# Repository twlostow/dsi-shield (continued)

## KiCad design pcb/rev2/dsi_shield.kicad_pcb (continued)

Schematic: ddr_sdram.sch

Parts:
C11, C65, C67, C71, C72, C73, C75: CC0603_100NF_100V_10%_X7R; CAPC1608X90N; Voltage 100V; Tolerance ±10%; Part Number CC0603_100NF_100V_10%_X7R
C64: CC0603_1UF_50V_10%_X5R; CAPC1608X87N; Voltage 50V; Tolerance ±10%; Part Number CC0603_1UF_50V_10%_X5R
C66, C68, C69, C70: CC0603_10NF_50V_10%_X7R; CAPC1608X87N; Voltage 50V; Tolerance ±10%; Part Number CC0603_10NF_50V_10%_X7R
IC10: MT46V32M16P-5B:F; TSOP66
R67: R0603_100R_1%_0.1W_100PPM; RESC1608X55N; Voltage ~~; Tolerance ±1%; Part Number R0603_100R_1%_0.1W_100PPM
R68, R69: R0603_1K_1%_0.1W_100PPM; RESC1608X55N; Voltage ~~; Tolerance ±1%; Part Number R0603_1K_1%_0.1W_100PPM

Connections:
+2V5: C11.1, C64.1, C65.1, C66.1, C67.1, C68.1, C69.1, C70.1, C72.1, C73.1, C75.1, IC10.1, IC10.3, IC10.9, IC10.15, IC10.18, IC10.33, IC10.55, IC10.61, R68.1; also elsewhere on the board
/DDR/DDR_VREF: C65.2, C71.1, IC10.49, R68.2, R69.1; also elsewhere on the board
/DDR/SDRAM_A0: IC10.29; also elsewhere on the board
/DDR/SDRAM_A1: IC10.30; also elsewhere on the board
/DDR/SDRAM_A2: IC10.31; also elsewhere on the board
/DDR/SDRAM_A3: IC10.32; also elsewhere on the board
/DDR/SDRAM_A4: IC10.35; also elsewhere on the board
/DDR/SDRAM_A5: IC10.36; also elsewhere on the board
/DDR/SDRAM_A6: IC10.37; also elsewhere on the board
/DDR/SDRAM_A7: IC10.38; also elsewhere on the board
/DDR/SDRAM_A8: IC10.39; also elsewhere on the board
/DDR/SDRAM_A9: IC10.40; also elsewhere on the board
/DDR/SDRAM_A10: IC10.28; also elsewhere on the board
/DDR/SDRAM_A11: IC10.41; also elsewhere on the board
/DDR/SDRAM_A12: IC10.42; also elsewhere on the board
/DDR/SDRAM_BA0: IC10.26; also elsewhere on the board
/DDR/SDRAM_BA1: IC10.27; also elsewhere on the board
/DDR/SDRAM_CAS_N: IC10.22; also elsewhere on the board
/DDR/SDRAM_CKE: IC10.44; also elsewhere on the board
/DDR/SDRAM_CLK_N: IC10.46, R67.2; also elsewhere on the board
/DDR/SDRAM_CLK_P: IC10.45, R67.1; also elsewhere on the board
/DDR/SDRAM_CS_N: IC10.24; also elsewhere on the board
/DDR/SDRAM_DQ0: IC10.2; also elsewhere on the board
/DDR/SDRAM_DQ1: IC10.4; also elsewhere on the board
/DDR/SDRAM_DQ2: IC10.5; also elsewhere on the board
/DDR/SDRAM_DQ3: IC10.7; also elsewhere on the board
/DDR/SDRAM_DQ4: IC10.8; also elsewhere on the board
/DDR/SDRAM_DQ5: IC10.10; also elsewhere on the board
/DDR/SDRAM_DQ6: IC10.11; also elsewhere on the board
/DDR/SDRAM_DQ7: IC10.13; also elsewhere on the board
/DDR/SDRAM_DQ8: IC10.54; also elsewhere on the board
/DDR/SDRAM_DQ9: IC10.56; also elsewhere on the board
/DDR/SDRAM_DQ10: IC10.57; also elsewhere on the board
/DDR/SDRAM_DQ11: IC10.59; also elsewhere on the board
/DDR/SDRAM_DQ12: IC10.60; also elsewhere on the board
/DDR/SDRAM_DQ13: IC10.62; also elsewhere on the board
/DDR/SDRAM_DQ14: IC10.63; also elsewhere on the board
/DDR/SDRAM_DQ15: IC10.65; also elsewhere on the board
/DDR/SDRAM_DQM0: IC10.20; also elsewhere on the board
/DDR/SDRAM_DQM1: IC10.47; also elsewhere on the board
/DDR/SDRAM_DQS0: IC10.16; also elsewhere on the board
/DDR/SDRAM_DQS1: IC10.51; also elsewhere on the board
/DDR/SDRAM_RAS_N: IC10.23; also elsewhere on the board
/DDR/SDRAM_WE_N: IC10.21; also elsewhere on the board
GND: C11.2, C64.2, C66.2, C67.2, C68.2, C69.2, C70.2, C71.2, C72.2, C73.2, C75.2, IC10.6, IC10.12, IC10.34, IC10.48, IC10.52, IC10.58, IC10.64, IC10.66, R69.2; also elsewhere on the board

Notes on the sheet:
Copyright 2013-2017 twl <twlostow@printf.cc> This documentation describes Open Hardware and is licensed under the CERN OHL v. 1.2. You may redistribute and modify this documentation under the terms of the CERN OHL v.1.2. (http://ohwr.org/CERNOHL). This documentation is distributed WITHOUT ANY EXPRE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
HDMI DSI Shield
DDR SDRAM
2.2a

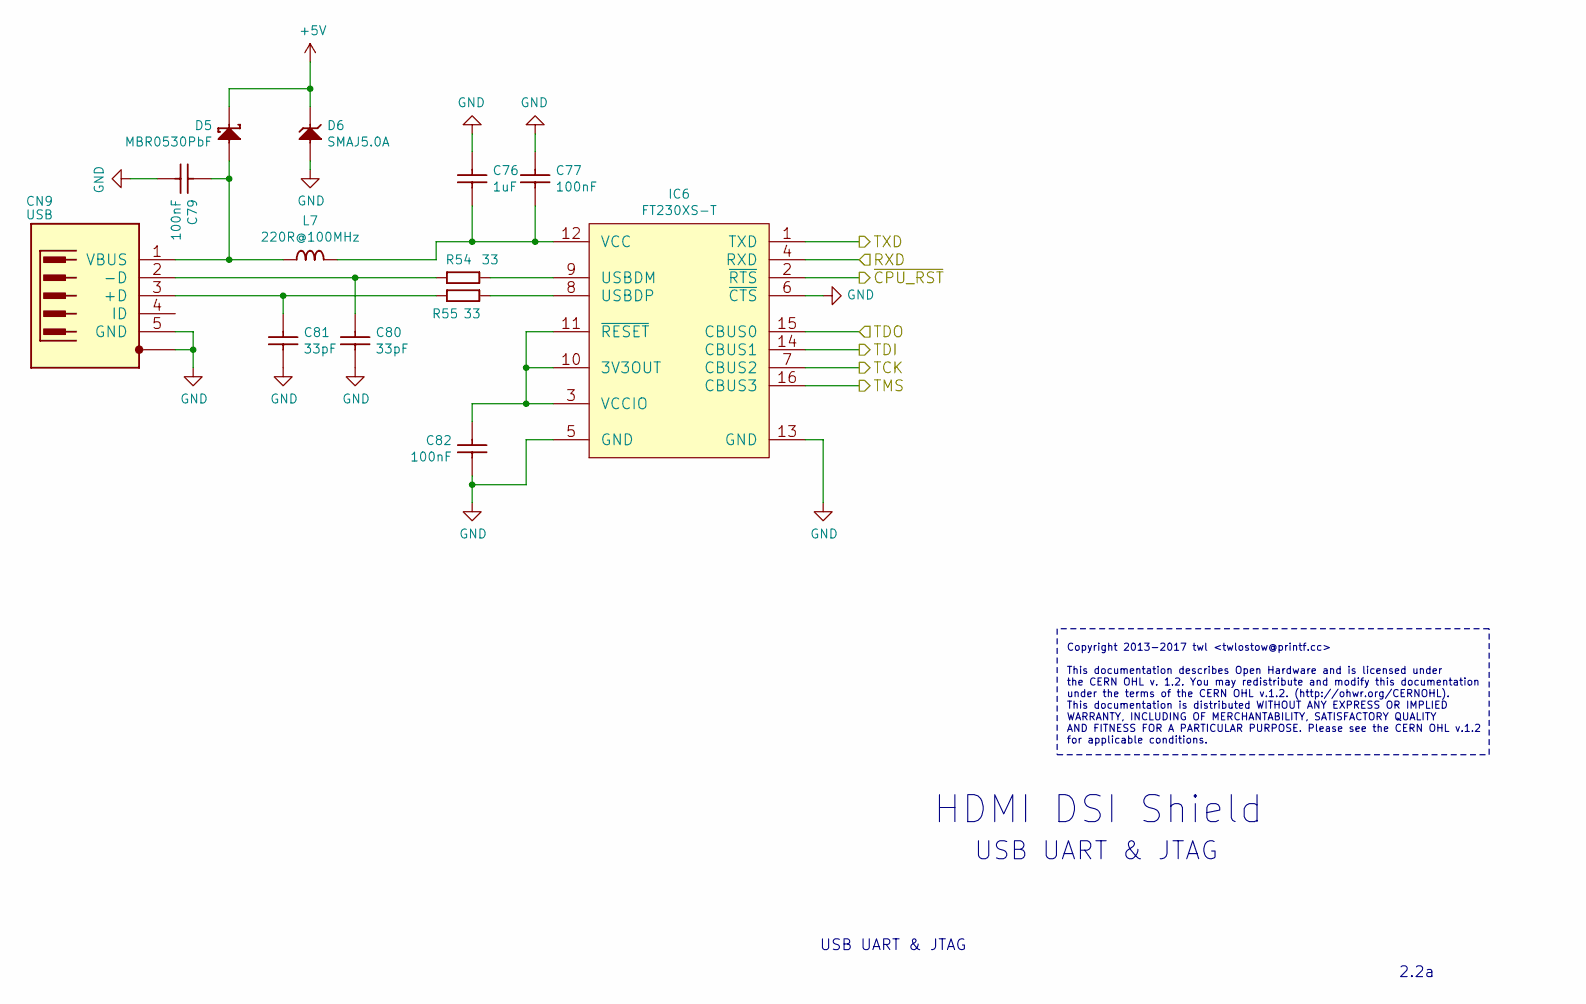
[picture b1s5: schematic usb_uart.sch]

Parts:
C76: CC0603_1UF_50V_10%_X5R; CAPC1608X87N; Voltage 50V; Tolerance ±10%; Part Number CC0603_1UF_50V_10%_X5R
C77, C79, C82: CC0603_100NF_100V_10%_X7R; CAPC1608X90N; Voltage 100V; Tolerance ±10%; Part Number CC0603_100NF_100V_10%_X7R
C80, C81: CC0603_33PF_50V_5%_NP0; CAPC1608X87N; Voltage 50V; Tolerance ±5%; Part Number CC0603_33PF_50V_5%_NP0
CN9: TYCO_1734035-1; Part Number TYCO_1734035-1
D5: MBR0530PbF; SOD3715X145N; Voltage 30V; Part Number MBR0530PbF
D6: SMAJ5.0A; DIOM5226X262N; Voltage 5V; Part Number SMAJ5.0A
IC6: FT230XS-T; SOP63P600X175-16N; Part Number FT230XS-T
L7: IND0805_MURATA_BLM21PG221SN1D; INDC2012X105N; Tolerance ±25%; Part Number IND0805_MURATA_BLM21PG221SN1D
R54, R55: R0603_33R_1%_0.1W_100PPM; RESC1608X55N; Voltage ~~; Tolerance ±1%; Part Number R0603_33R_1%_0.1W_100PPM

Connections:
+5V: D5.1 (C), D6.1 (C); also elsewhere on the board
/CPU_RST_N: IC6.2 (~RTS); also elsewhere on the board
/FPGA/DBG_RX: IC6.1 (TXD); also elsewhere on the board
/FPGA/DBG_TX: IC6.4 (RXD); also elsewhere on the board
/FPGA/TCK: IC6.7 (CBUS2); also elsewhere on the board
/FPGA/TDI: IC6.14 (CBUS1); also elsewhere on the board
/FPGA/TDO: IC6.15 (CBUS0); also elsewhere on the board
/FPGA/TMS: IC6.16 (CBUS3); also elsewhere on the board
GND: C76.1, C77.1, C79.2, C80.2, C81.2, C82.2, CN9.5 (GND), CN9.6 (SH), D6.2 (A), IC6.5 (GND), IC6.6 (~CTS), IC6.13 (GND); also elsewhere on the board
unnamed: C76.2, C77.2, IC6.12 (VCC), L7.2
unnamed: C79.1, CN9.1 (VBUS), D5.2 (A), L7.1
unnamed: C80.1, CN9.2 (-D), R54.1
unnamed: C81.1, CN9.3 (+D), R55.1
unnamed: C82.1, IC6.3 (VCCIO), IC6.10 (3V3OUT), IC6.11 (~RESET)
unnamed: IC6.8 (USBDP), R55.2
unnamed: IC6.9 (USBDM), R54.2

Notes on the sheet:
HDMI DSI Shield
USB UART & JTAG
2.2a
Copyright 2013-2017 twl <twlostow@printf.cc> This documentation describes Open Hardware and is licensed under the CERN OHL v. 1.2. You may redistribute and modify this documentation under the terms of the CERN OHL v.1.2. (http://ohwr.org/CERNOHL). This documentation is distributed WITHOUT ANY EXPRE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

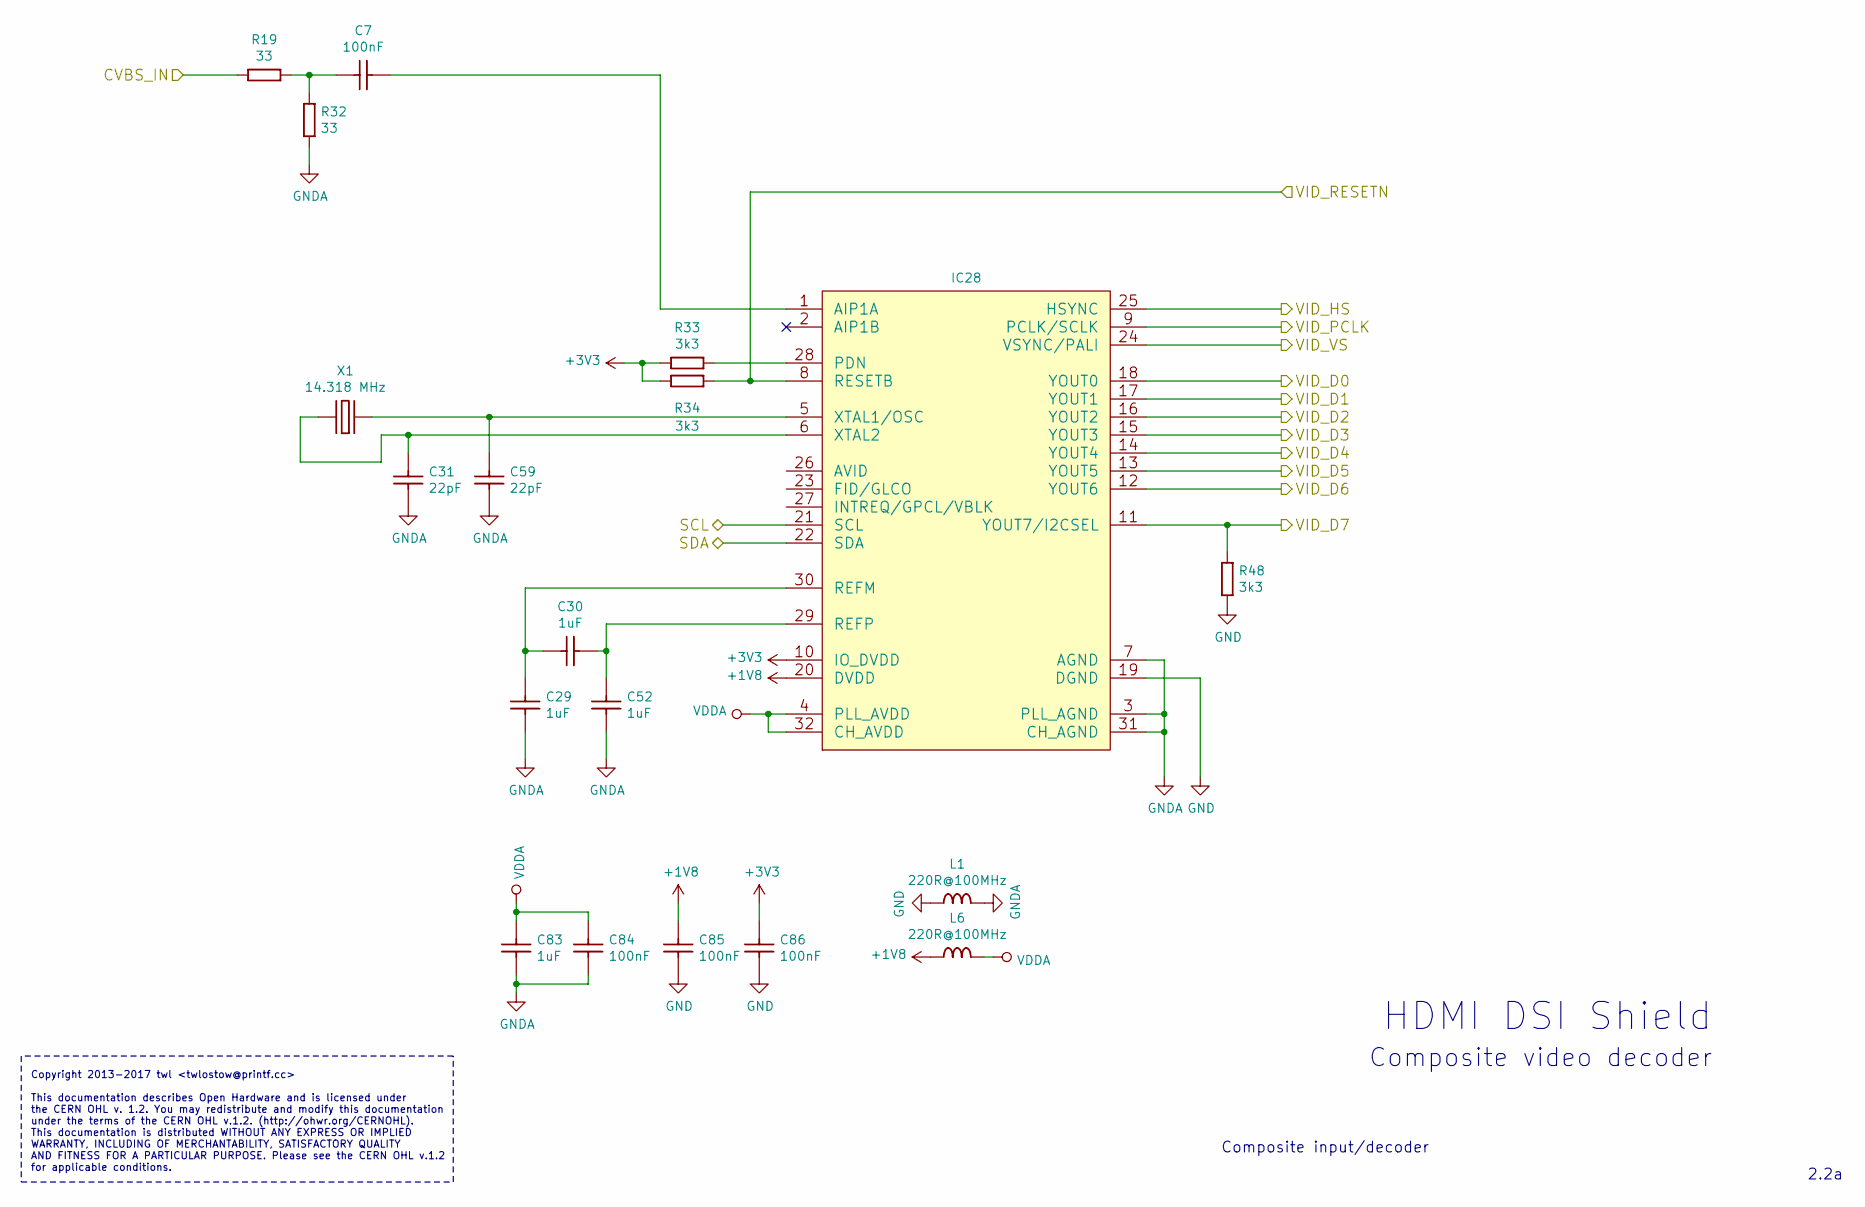
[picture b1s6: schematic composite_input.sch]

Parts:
C7, C84, C85, C86: CC0603_100NF_100V_10%_X7R; CAPC1608X90N; Voltage 100V; Tolerance ±10%; Part Number CC0603_100NF_100V_10%_X7R
C29, C30, C52, C83: CC0603_1UF_50V_10%_X5R; CAPC1608X87N; Voltage 50V; Tolerance ±10%; Part Number CC0603_1UF_50V_10%_X5R
C31, C59: CC0603_22PF_50V_5%_NP0; CAPC1608X87N; Voltage 50V; Tolerance ±5%; Part Number CC0603_22PF_50V_5%_NP0
IC28: TVP5150AM1PBS; TSQFP50P700X700-32L
L1, L6: IND0805_MURATA_BLM21PG221SN1D; INDC2012X105N; Tolerance ±25%; Part Number IND0805_MURATA_BLM21PG221SN1D
R19, R32: R0603_33R_1%_0.1W_100PPM; RESC1608X55N; Voltage ~~; Tolerance ±1%; Part Number R0603_33R_1%_0.1W_100PPM
R33, R34, R48: R0603_3K3_1%_0.1W_100PPM; RESC1608X55N; Voltage ~~; Tolerance ±1%; Part Number R0603_3K3_1%_0.1W_100PPM
X1: XTAL_12MHZ_TXC_7A-14.31818MAAJ-T; XTAL_TXC_7A; Part Number XTAL_12MHZ_TXC_7A-14.31818MAAJ-T

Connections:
+1V8: C85.1, IC28.20 (DVDD), L6.1; also elsewhere on the board
/COMP_IN/CVBS_IN: R19.1; also elsewhere on the board
/HOST_A0: IC28.8 (RESETB), R34.2; also elsewhere on the board
/HOST_CS: IC28.12 (YOUT6); also elsewhere on the board
/HOST_D0: IC28.14 (YOUT4); also elsewhere on the board
/HOST_D1: IC28.15 (YOUT3); also elsewhere on the board
/HOST_D2: IC28.16 (YOUT2); also elsewhere on the board
/HOST_D3: IC28.18 (YOUT0); also elsewhere on the board
/HOST_D4: IC28.24 (VSYNC/PALI); also elsewhere on the board
/HOST_D5: IC28.13 (YOUT5); also elsewhere on the board
/HOST_D6: IC28.17 (YOUT1); also elsewhere on the board
/HOST_D7: IC28.25 (HSYNC); also elsewhere on the board
/HOST_RD: IC28.11 (YOUT7/I2CSEL), R48.1; also elsewhere on the board
/HOST_WE: IC28.9 (PCLK/SCLK); also elsewhere on the board
/SCL: IC28.21 (SCL); also elsewhere on the board
/SDA: IC28.22 (SDA); also elsewhere on the board
GND: C85.2, C86.2, IC28.19 (DGND), L1.1, R48.2; also elsewhere on the board
GNDA: C29.2, C31.2, C52.1, C59.2, C83.2, C84.2, IC28.3 (PLL_AGND), IC28.7 (AGND), IC28.31 (CH_AGND), L1.2, R32.2; also elsewhere on the board
unnamed: C7.1, R19.2, R32.1
unnamed: C7.2, IC28.1 (AIP1A)
unnamed: C29.1, C30.2, IC28.30 (REFM)
unnamed: C30.1, C52.2, IC28.29 (REFP)
unnamed: C31.1, IC28.6 (XTAL2), X1.1 (OSC1)
unnamed: C59.1, IC28.5 (XTAL1/OSC), X1.2 (OSC2)
unnamed: IC28.28 (PDN), R33.2
VDDA: C83.1, C84.1, IC28.4 (PLL_AVDD), IC28.32 (CH_AVDD), L6.2

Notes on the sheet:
Copyright 2013-2017 twl <twlostow@printf.cc> This documentation describes Open Hardware and is licensed under the CERN OHL v. 1.2. You may redistribute and modify this documentation under the terms of the CERN OHL v.1.2. (http://ohwr.org/CERNOHL). This documentation is distributed WITHOUT ANY EXPRE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
HDMI DSI Shield
Composite video decoder
2.2a
Composite input/decoder

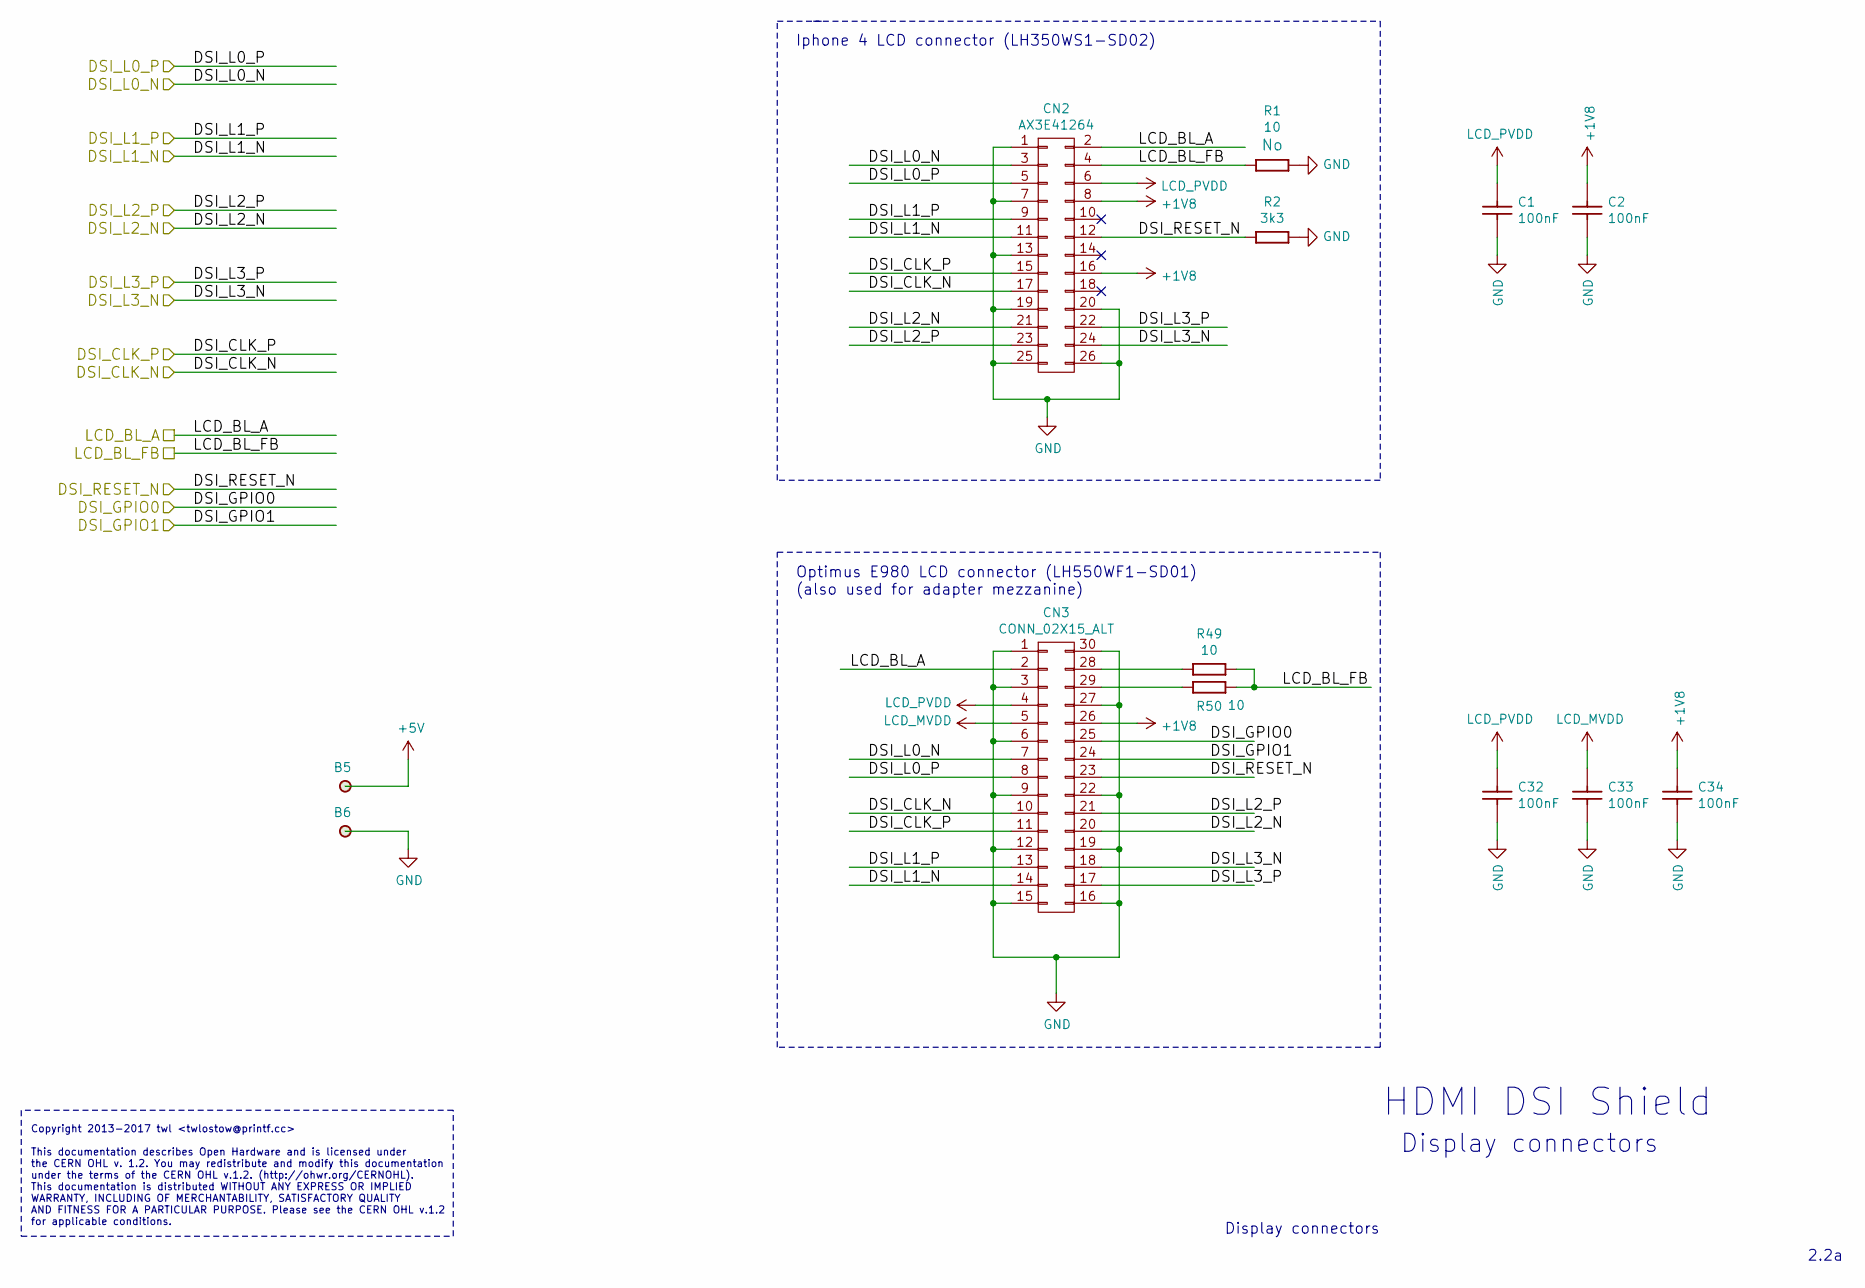
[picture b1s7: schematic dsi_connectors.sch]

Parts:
B5, B6: PLATED_HOLE0.8_PAD1.3; c130h80; Part Number PLATED_HOLE0.8_PAD1.3
C1, C2, C32, C33, C34: CC0603_100NF_100V_10%_X7R; CAPC1608X90N; Voltage 100V; Tolerance ±10%; Part Number CC0603_100NF_100V_10%_X7R
CN2: AX3E41264; IPHONE4_LCD_CONN
CN3: CONN_02X15_ALT; GB042-30S-E1000
R1, R49, R50: R0603_10R_1%_0.1W_200PPM; RESC1608X55N; Voltage ~~; Tolerance ±1%; Part Number R0603_10R_1%_0.1W_200PPM
R2: R0603_3K3_1%_0.1W_100PPM; RESC1608X55N; Voltage ~~; Tolerance ±1%; Part Number R0603_3K3_1%_0.1W_100PPM

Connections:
+1V8: C2.1, C34.1, CN2.8, CN2.16, CN3.26; also elsewhere on the board
+5V: B5.1; also elsewhere on the board
/CONN/DSI_CLK_N: CN2.17, CN3.10; also elsewhere on the board
/CONN/DSI_CLK_P: CN2.15, CN3.11; also elsewhere on the board
/CONN/DSI_GPIO0: CN3.25; also elsewhere on the board
/CONN/DSI_GPIO1: CN3.24; also elsewhere on the board
/CONN/DSI_L0_N: CN2.3, CN3.7; also elsewhere on the board
/CONN/DSI_L0_P: CN2.5, CN3.8; also elsewhere on the board
/CONN/DSI_L1_N: CN2.11, CN3.14; also elsewhere on the board
/CONN/DSI_L1_P: CN2.9, CN3.13; also elsewhere on the board
/CONN/DSI_L2_N: CN2.21, CN3.20; also elsewhere on the board
/CONN/DSI_L2_P: CN2.23, CN3.21; also elsewhere on the board
/CONN/DSI_L3_N: CN2.24, CN3.18; also elsewhere on the board
/CONN/DSI_L3_P: CN2.22, CN3.17; also elsewhere on the board
/CONN/DSI_RESET_N: CN2.12, CN3.23, R2.1; also elsewhere on the board
/CONN/LCD_BL_A: CN2.2, CN3.2; also elsewhere on the board
/CONN/LCD_BL_FB: CN2.4, R1.1, R49.2, R50.2; also elsewhere on the board
GND: B6.1, C1.2, C2.2, C32.2, C33.2, C34.2, CN2.1, CN2.7, CN2.13, CN2.19, CN2.20, CN2.25, CN2.26, CN3.1, CN3.3, CN3.6, CN3.9, CN3.12, CN3.15, CN3.16, CN3.19, CN3.22, CN3.27, CN3.30, R1.2, R2.2; also elsewhere on the board
LCD_MVDD: C33.1, CN3.5; also elsewhere on the board
LCD_PVDD: C1.1, C32.1, CN2.6, CN3.4; also elsewhere on the board
unnamed: CN3.28, R49.1
unnamed: CN3.29, R50.1

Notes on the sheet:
Iphone 4 LCD connector (LH350WS1-SD02)
Optimus E980 LCD connector (LH550WF1-SD01) (also used for adapter mezzanine)
HDMI DSI Shield
Display connectors
2.2a
Copyright 2013-2017 twl <twlostow@printf.cc> This documentation describes Open Hardware and is licensed under the CERN OHL v. 1.2. You may redistribute and modify this documentation under the terms of the CERN OHL v.1.2. (http://ohwr.org/CERNOHL). This documentation is distributed WITHOUT ANY EXPRE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

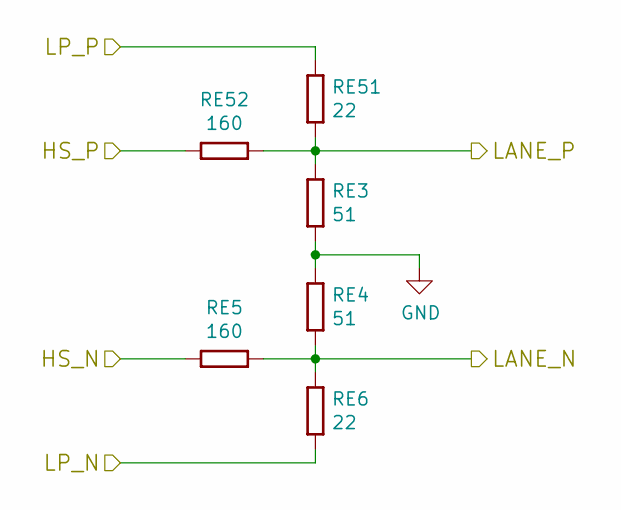
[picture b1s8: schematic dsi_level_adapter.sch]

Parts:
RA3, RA4: R0603_51R_1%_0.1W_100PPM; RESC1608X55N; Voltage ~~; Tolerance ±1%; Part Number R0603_51R_1%_0.1W_100PPM
RA5, RA52: R0603_160R_1%_0.1W_100PPM; RESC1608X55N; Voltage ~~; Tolerance ±1%; Part Number R0603_160R_1%_0.1W_100PPM
RA6, RA51: R0603_22R_1%_0.1W_100PPM; RESC1608X55N; Voltage ~~; Tolerance ±1%; Part Number R0603_22R_1%_0.1W_100PPM

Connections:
/CONN/DSI_L0_N: RA4.2, RA5.1, RA6.1; also elsewhere on the board
/CONN/DSI_L0_P: RA3.1, RA51.2, RA52.1; also elsewhere on the board
/FPGA/DSI_HS_N0: RA5.2; also elsewhere on the board
/FPGA/DSI_HS_P0: RA52.2; also elsewhere on the board
/FPGA/DSI_LP_N0: RA6.2; also elsewhere on the board
/FPGA/DSI_LP_P0: RA51.1; also elsewhere on the board
GND: RA3.2, RA4.1; also elsewhere on the board

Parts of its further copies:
RB3, RB4: R0603_51R_1%_0.1W_100PPM; RESC1608X55N; Voltage ~~; Tolerance ±1%; Part Number R0603_51R_1%_0.1W_100PPM
RB5, RB52: R0603_160R_1%_0.1W_100PPM; RESC1608X55N; Voltage ~~; Tolerance ±1%; Part Number R0603_160R_1%_0.1W_100PPM
RB6, RB51: R0603_22R_1%_0.1W_100PPM; RESC1608X55N; Voltage ~~; Tolerance ±1%; Part Number R0603_22R_1%_0.1W_100PPM
RC3, RC4: R0603_51R_1%_0.1W_100PPM; RESC1608X55N; Voltage ~~; Tolerance ±1%; Part Number R0603_51R_1%_0.1W_100PPM
RC5, RC52: R0603_160R_1%_0.1W_100PPM; RESC1608X55N; Voltage ~~; Tolerance ±1%; Part Number R0603_160R_1%_0.1W_100PPM
RC6, RC51: R0603_22R_1%_0.1W_100PPM; RESC1608X55N; Voltage ~~; Tolerance ±1%; Part Number R0603_22R_1%_0.1W_100PPM
RD3, RD4: R0603_51R_1%_0.1W_100PPM; RESC1608X55N; Voltage ~~; Tolerance ±1%; Part Number R0603_51R_1%_0.1W_100PPM
RD5, RD52: R0603_160R_1%_0.1W_100PPM; RESC1608X55N; Voltage ~~; Tolerance ±1%; Part Number R0603_160R_1%_0.1W_100PPM
RD6, RD51: R0603_22R_1%_0.1W_100PPM; RESC1608X55N; Voltage ~~; Tolerance ±1%; Part Number R0603_22R_1%_0.1W_100PPM
RE3, RE4: R0603_51R_1%_0.1W_100PPM; RESC1608X55N; Voltage ~~; Tolerance ±1%; Part Number R0603_51R_1%_0.1W_100PPM
RE5, RE52: R0603_160R_1%_0.1W_100PPM; RESC1608X55N; Voltage ~~; Tolerance ±1%; Part Number R0603_160R_1%_0.1W_100PPM
RE6, RE51: R0603_22R_1%_0.1W_100PPM; RESC1608X55N; Voltage ~~; Tolerance ±1%; Part Number R0603_22R_1%_0.1W_100PPM

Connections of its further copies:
/CONN/DSI_CLK_N: RE4.2, RE5.1, RE6.1; also elsewhere on the board
/CONN/DSI_CLK_P: RE3.1, RE51.2, RE52.1; also elsewhere on the board
/CONN/DSI_L1_N: RB4.2, RB5.1, RB6.1; also elsewhere on the board
/CONN/DSI_L1_P: RB3.1, RB51.2, RB52.1; also elsewhere on the board
/CONN/DSI_L2_N: RC4.2, RC5.1, RC6.1; also elsewhere on the board
/CONN/DSI_L2_P: RC3.1, RC51.2, RC52.1; also elsewhere on the board
/CONN/DSI_L3_N: RD4.2, RD5.1, RD6.1; also elsewhere on the board
/CONN/DSI_L3_P: RD3.1, RD51.2, RD52.1; also elsewhere on the board
/FPGA/DSI_HS_CLK_N: RE5.2; also elsewhere on the board
/FPGA/DSI_HS_CLK_P: RE52.2; also elsewhere on the board
/FPGA/DSI_HS_N1: RB5.2; also elsewhere on the board
/FPGA/DSI_HS_N2: RC5.2; also elsewhere on the board
/FPGA/DSI_HS_N3: RD5.2; also elsewhere on the board
/FPGA/DSI_HS_P1: RB52.2; also elsewhere on the board
/FPGA/DSI_HS_P2: RC52.2; also elsewhere on the board
/FPGA/DSI_HS_P3: RD52.2; also elsewhere on the board
/FPGA/DSI_LP_CLK_N: RE6.2; also elsewhere on the board
/FPGA/DSI_LP_CLK_P: RE51.1; also elsewhere on the board
/FPGA/DSI_LP_N1: RB6.2; also elsewhere on the board
/FPGA/DSI_LP_N2: RC6.2; also elsewhere on the board
/FPGA/DSI_LP_N3: RD6.2; also elsewhere on the board
/FPGA/DSI_LP_P1: RB51.1; also elsewhere on the board
/FPGA/DSI_LP_P2: RC51.1; also elsewhere on the board
/FPGA/DSI_LP_P3: RD51.1; also elsewhere on the board
GND: RB3.2, RB4.1, RC3.2, RC4.1, RD3.2, RD4.1, RE3.2, RE4.1; also elsewhere on the board

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
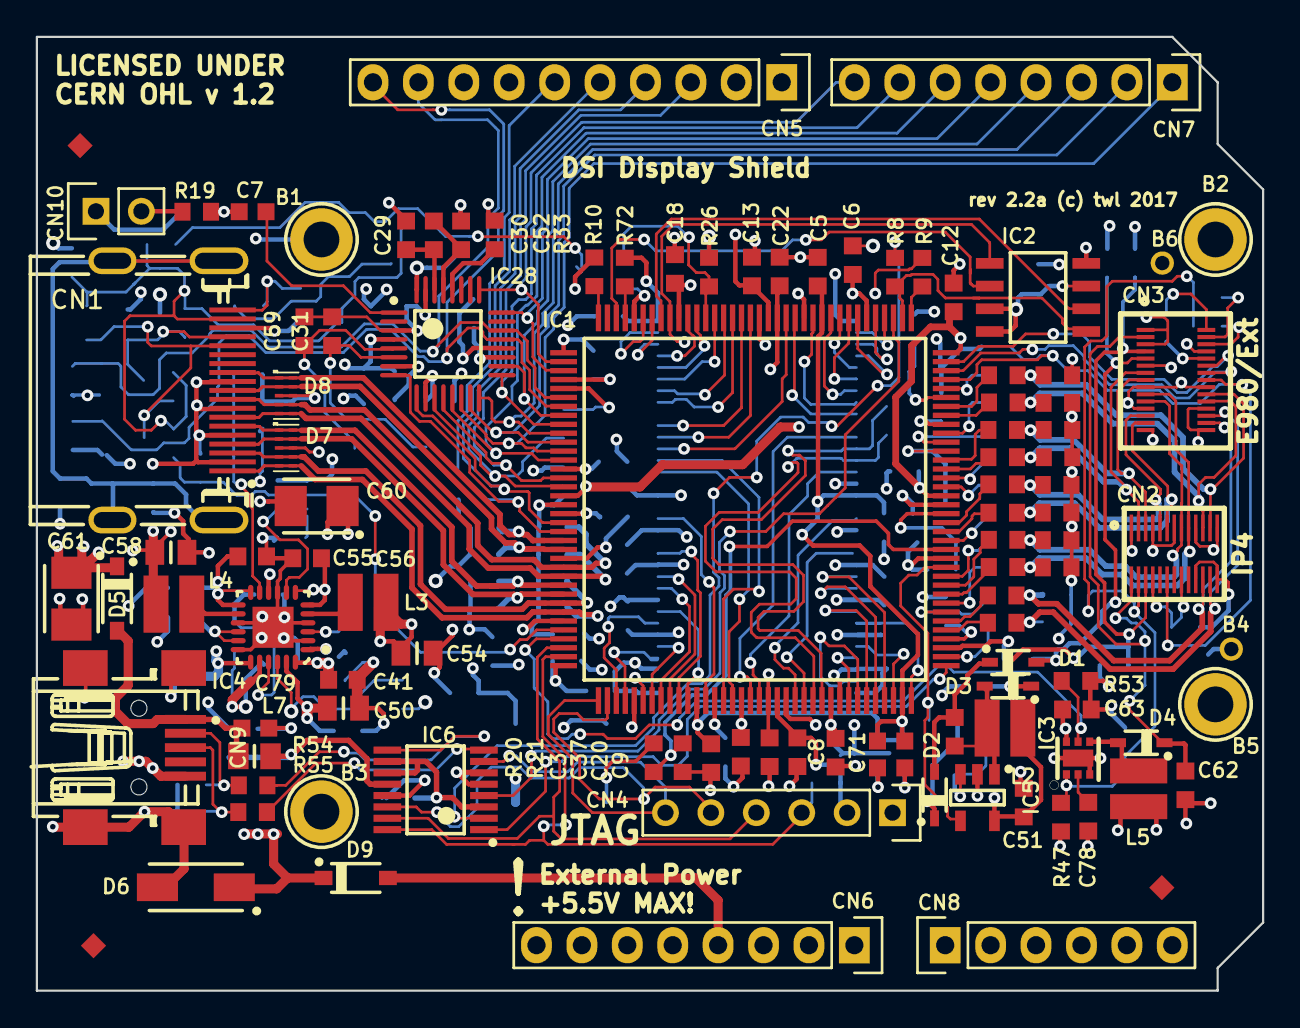
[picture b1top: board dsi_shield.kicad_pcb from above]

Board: 4 copper layers, 68.6 x 53.3 mm, 224 parts (0 on the bottom side), 167 nets.

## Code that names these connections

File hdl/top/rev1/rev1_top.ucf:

NET "clk_25m_i" LOC = P14;
NET "clk_25m_i" IOSTANDARD = LVCMOS18;

NET "uart_rxd_i" LOC = P1;
NET "uart_rxd_i" IOSTANDARD = LVCMOS18;

NET "uart_txd_o" LOC = P39;
NET "uart_txd_o" IOSTANDARD = LVCMOS25;

NET "clk_25m_i" TNM_NET = "clk_25m_i";
TIMESPEC TS_clk_25m_i = PERIOD "clk_25m_i" 25 MHz HIGH 50 %;

#Orsons's Galaxy S4 adapter (lanes swapped)



NET "dsi_clk_p_o" LOC = P30; 
NET "dsi_clk_n_o" LOC = P29;

NET "dsi_hs_p_o[0]" LOC = P6;
NET "dsi_hs_n_o[0]" LOC = P5;

NET "dsi_hs_p_o[1]" LOC = P24;
NET "dsi_hs_n_o[1]" LOC = P23;

NET "dsi_hs_p_o[2]" LOC = P17;
NET "dsi_hs_n_o[2]" LOC = P16;

NET "dsi_hs_p_o[3]" LOC = P10;
NET "dsi_hs_n_o[3]" LOC = P9;



NET "dsi_lp_p_o[0]" LOC = P7;
NET "dsi_lp_p_o[0]" IOSTANDARD = LVCMOS18;

NET "dsi_lp_n_o[0]" LOC = P2;
NET "dsi_lp_n_o[0]" IOSTANDARD = LVCMOS18;

NET "dsi_lp_p_o[1]" LOC = P26;
NET "dsi_lp_p_o[1]" IOSTANDARD = LVCMOS18;

NET "dsi_lp_n_o[1]" LOC = P22;
NET "dsi_lp_n_o[1]" IOSTANDARD = LVCMOS18;

NET "dsi_lp_p_o[2]" LOC = P21;
NET "dsi_lp_p_o[2]" IOSTANDARD = LVCMOS18;

NET "dsi_lp_n_o[2]" LOC = P15;
NET "dsi_lp_n_o[2]" IOSTANDARD = LVCMOS18;

NET "dsi_lp_p_o[3]" LOC = P11;
NET "dsi_lp_p_o[3]" IOSTANDARD = LVCMOS18;

NET "dsi_lp_n_o[3]" LOC = P8;
NET "dsi_lp_n_o[3]" IOSTANDARD = LVCMOS18;

NET "dsi_clk_lp_p_o" LOC = P32;
NET "dsi_clk_lp_p_o" IOSTANDARD = LVCMOS18;

NET "dsi_clk_lp_n_o" LOC = P27;
NET "dsi_clk_lp_n_o" IOSTANDARD = LVCMOS18;


#original definitions (for DNA, Iphone, P880 adapters)

#NET "dsi_clk_p_o" LOC = P17;
#15_p
#NET "dsi_clk_n_o" LOC = P16;
#15_n
#NET "dsi_hs_p_o[0]" LOC = P30;
#30_p
#NET "dsi_hs_n_o[0]" LOC = P29;
#30_n
#NET "dsi_hs_p_o[1]" LOC = P24;
#24_p
#NET "dsi_hs_n_o[1]" LOC = P23;
#24_n
#NET "dsi_hs_p_o[2]" LOC = P10;
#07p
#NET "dsi_hs_n_o[2]" LOC = P9;
#07n
#NET "dsi_hs_p_o[3]" LOC = P6;
#07p
#NET "dsi_hs_n_o[3]" LOC = P5;
#07n
#NET "dsi_lp_p_o[0]" LOC = P32;
#28_n
#NET "dsi_lp_p_o[0]" IOSTANDARD = LVCMOS18;

#NET "dsi_lp_n_o[0]" LOC = P27;
#32_p
#NET "dsi_lp_n_o[0]" IOSTANDARD = LVCMOS18;

#NET "dsi_lp_p_o[1]" LOC = P26;
#21_n
#NET "dsi_lp_p_o[1]" IOSTANDARD = LVCMOS18;

#NET "dsi_lp_n_o[1]" LOC = P22;
#28_p
#NET "dsi_lp_n_o[1]" IOSTANDARD = LVCMOS18;

#NET "dsi_lp_p_o[2]" LOC = P11;
#4_n
#NET "dsi_lp_p_o[2]" IOSTANDARD = LVCMOS18;

#NET "dsi_lp_n_o[2]" LOC = P8;
#11_p
#NET "dsi_lp_n_o[2]" IOSTANDARD = LVCMOS18;

#NET "dsi_lp_p_o[3]" LOC = P7;
#4_n
#NET "dsi_lp_p_o[3]" IOSTANDARD = LVCMOS18;

#NET "dsi_lp_n_o[3]" LOC = P2;
#11_p
#NET "dsi_lp_n_o[3]" IOSTANDARD = LVCMOS18;


#NET "dsi_clk_lp_p_o" LOC = P21;
#11_n
#NET "dsi_clk_lp_p_o" IOSTANDARD = LVCMOS18;

#NET "dsi_clk_lp_n_o" LOC = P15;
#19_p
#NET "dsi_clk_lp_n_o" IOSTANDARD = LVCMOS18;

NET "dsi_resetb_o" LOC = P35;
#04_p
NET "dsi_resetb_o" IOSTANDARD = LVCMOS18;


NET "dsi_gpio1_o" LOC = P34;
#02_n
NET "dsi_gpio1_o" IOSTANDARD = LVCMOS18;

NET "dsi_gpio0_o" LOC = P33;
#02_p
NET "dsi_gpio0_o" IOSTANDARD = LVCMOS18;

NET "lcd_pwren_o" LOC = P12;
NET "lcd_pwren_o" IOSTANDARD = LVCMOS18;


NET "dsi_clk_lp_n_o" DRIVE = 24;
NET "dsi_clk_lp_p_o" DRIVE = 24;
NET "dsi_lp_n_o[0]" DRIVE = 24;
NET "dsi_lp_n_o[1]" DRIVE = 24;
NET "dsi_lp_n_o[2]" DRIVE = 24;
NET "dsi_lp_n_o[3]" DRIVE = 24;
NET "dsi_lp_p_o[0]" DRIVE = 24;
NET "dsi_lp_p_o[1]" DRIVE = 24;
NET "dsi_lp_p_o[2]" DRIVE = 24;
NET "dsi_lp_p_o[3]" DRIVE = 24;



NET "rst_n_a_i" LOC = P38;
NET "rst_n_a_i" IOSTANDARD = LVCMOS25;


NET "sdram_adr[0]" LOC = P61;
NET "sdram_adr[1]" LOC = P62;
NET "sdram_adr[2]" LOC = P66;
NET "sdram_adr[3]" LOC = P67;
NET "sdram_adr[4]" LOC = P40;
NET "sdram_adr[5]" LOC = P41;
NET "sdram_adr[6]" LOC = P43;
NET "sdram_adr[7]" LOC = P45;
NET "sdram_adr[8]" LOC = P44;
NET "sdram_adr[9]" LOC = P46;
NET "sdram_adr[10]" LOC = P59;
NET "sdram_adr[11]" LOC = P48;
NET "sdram_adr[12]" LOC = P50;
NET "sdram_ba[0]" LOC = P57;
NET "sdram_ba[1]" LOC = P58;
NET "sdram_cas_n" LOC = P51;
NET "sdram_cke" LOC = P126;
NET "sdram_clk_n" LOC = P133;
NET "sdram_clk_p" LOC = P134;
NET "sdram_cs_n" LOC = P56;
NET "sdram_dm[0]" LOC = P124;
NET "sdram_dm[1]" LOC = P127;
NET "sdram_dq[0]" LOC = P114;
NET "sdram_dq[1]" LOC = P112;
NET "sdram_dq[2]" LOC = P115;
NET "sdram_dq[3]" LOC = P111;
NET "sdram_dq[4]" LOC = P119;
NET "sdram_dq[5]" LOC = P116;
NET "sdram_dq[6]" LOC = P117;
NET "sdram_dq[7]" LOC = P118;
NET "sdram_dq[8]" LOC = P132;
NET "sdram_dq[9]" LOC = P141;
NET "sdram_dq[10]" LOC = P140;
NET "sdram_dq[11]" LOC = P139;
NET "sdram_dq[12]" LOC = P144;
NET "sdram_dq[13]" LOC = P142;
NET "sdram_dq[14]" LOC = P137;
NET "sdram_dq[15]" LOC = P138;
NET "sdram_dqs[0]" LOC = P121;
NET "sdram_dqs[1]" LOC = P131;
NET "sdram_ras_n" LOC = P55;
NET "sdram_we_n" LOC = P123;


NET "sdram_adr[0]" IOSTANDARD = SSTL2_II;
NET "sdram_adr[1]" IOSTANDARD = SSTL2_II;
NET "sdram_adr[2]" IOSTANDARD = SSTL2_II;
NET "sdram_adr[3]" IOSTANDARD = SSTL2_II;
NET "sdram_adr[4]" IOSTANDARD = SSTL2_II;
NET "sdram_adr[5]" IOSTANDARD = SSTL2_II;
NET "sdram_adr[6]" IOSTANDARD = SSTL2_II;
NET "sdram_adr[7]" IOSTANDARD = SSTL2_II;
NET "sdram_adr[8]" IOSTANDARD = SSTL2_II;
NET "sdram_adr[9]" IOSTANDARD = SSTL2_II;
NET "sdram_adr[10]" IOSTANDARD = SSTL2_II;
NET "sdram_adr[11]" IOSTANDARD = SSTL2_II;
NET "sdram_adr[12]" IOSTANDARD = SSTL2_II;
NET "sdram_ba[0]" IOSTANDARD = SSTL2_II;
NET "sdram_ba[1]" IOSTANDARD = SSTL2_II;
NET "sdram_cas_n" IOSTANDARD = SSTL2_II;
NET "sdram_cke" IOSTANDARD = SSTL2_II;
NET "sdram_clk_n" IOSTANDARD = DIFF_SSTL2_II;
NET "sdram_clk_p" IOSTANDARD = DIFF_SSTL2_II;
NET "sdram_cs_n" IOSTANDARD = SSTL2_II;
NET "sdram_dm[0]" IOSTANDARD = SSTL2_II;
NET "sdram_dm[1]" IOSTANDARD = SSTL2_II;
NET "sdram_dq[0]" IOSTANDARD = SSTL2_II;
NET "sdram_dq[1]" IOSTANDARD = SSTL2_II;
NET "sdram_dq[2]" IOSTANDARD = SSTL2_II;
NET "sdram_dq[3]" IOSTANDARD = SSTL2_II;
NET "sdram_dq[4]" IOSTANDARD = SSTL2_II;
NET "sdram_dq[5]" IOSTANDARD = SSTL2_II;
NET "sdram_dq[6]" IOSTANDARD = SSTL2_II;
NET "sdram_dq[7]" IOSTANDARD = SSTL2_II;
NET "sdram_dq[8]" IOSTANDARD = SSTL2_II;
NET "sdram_dq[9]" IOSTANDARD = SSTL2_II;
NET "sdram_dq[10]" IOSTANDARD = SSTL2_II;
NET "sdram_dq[11]" IOSTANDARD = SSTL2_II;
NET "sdram_dq[12]" IOSTANDARD = SSTL2_II;
NET "sdram_dq[13]" IOSTANDARD = SSTL2_II;
NET "sdram_dq[14]" IOSTANDARD = SSTL2_II;
NET "sdram_dq[15]" IOSTANDARD = SSTL2_II;
NET "sdram_dqs[0]" IOSTANDARD = SSTL2_II;
NET "sdram_dqs[1]" IOSTANDARD = SSTL2_II;
NET "sdram_ras_n" IOSTANDARD = SSTL2_II;
NET "sdram_we_n" IOSTANDARD = SSTL2_II;

TIMESPEC ts_ignore_xclock1 = FROM "U_PLL_clkout1" TO "U_PLL_clkout2" 4 ns DATAPATHONLY;
TIMESPEC ts_ignore_xclock2 = FROM "U_PLL_clkout2" TO "U_PLL_clkout1" 4 ns DATAPATHONLY;

NET "hdmi_rx_p_i[0]" LOC=P81;
NET "hdmi_rx_p_i[1]" LOC=P93;
NET "hdmi_rx_p_i[2]" LOC=P100;
NET "hdmi_rx_p_i[3]" LOC=P85;
NET "hdmi_rx_p_i[0]" IOSTANDARD=TMDS_33;
NET "hdmi_rx_p_i[1]" IOSTANDARD=TMDS_33;
NET "hdmi_rx_p_i[2]" IOSTANDARD=TMDS_33;
NET "hdmi_rx_p_i[3]" IOSTANDARD=TMDS_33;
 
NET "hdmi_scl_b" LOC=P74;
NET "hdmi_sda_b" LOC=P75;
NET "hdmi_hpd_o" LOC=P60;
NET "hdmi_p5v_notif_i" LOC=P87;
NET "hdmi_scl_b" IOSTANDARD = LVCMOS33;
NET "hdmi_sda_b" IOSTANDARD = LVCMOS33;
NET "hdmi_hpd_o" IOSTANDARD = LVCMOS25;	
NET "hdmi_p5v_notif_i" IOSTANDARD = LVCMOS33;

CONFIG VCCAUX=3.3;
#Created by Constraints Editor (xc6slx9-tqg144-2) - 2014/07/31
NET "hdmi_rx_p_i<3>" TNM_NET = hdmi_rx_p_i<3>;
TIMESPEC TS_hdmi_rx_p_i_3_ = PERIOD "hdmi_rx_p_i<3>" 12 ns HIGH 50%;
NET "hdmi_rx_n_i<3>" TNM_NET = hdmi_rx_n_i<3>;
TIMESPEC TS_hdmi_rx_n_i_3_ = PERIOD "hdmi_rx_n_i<3>" 12 ns HIGH 50%;
TIMESPEC ts_ignore_xclock3 = FROM "hdmi_rx_p_i<3>" TO "U_PLL_clkout2" 4 ns DATAPATHONLY;
TIMESPEC ts_ignore_xlock4 = FROM "U_PLL_clkout2" TO "hdmi_rx_p_i<3>" 4 ns DATAPATHONLY;

NET "*/gc_sync_register_in[*]" MAXDELAY=4ns;
#INST "hdmi_scl_b" IOB=FALSE;
#INST "hdmi_sda_b" IOB=FALSE;

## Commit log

2014-08-16 rev 1.0, release candidate (PCB+HDL+Software)
2014-08-19 software/rev1: use Iphone4 screen by default. Removed delays during LCD initialization.
2014-08-19 hdl/top/rev1: added table with PLL configs for different displays
2014-08-20 hdl: info where to find removed sources
2014-12-11 pcb: added component designators
2015-03-16 trying to get gs4 amoled screen to work...
2015-03-17 syn: python script for trying out different PLL frequencies
2015-03-17 trying to hack the EDID to make it look like Oculus DK2
2015-03-17 fake Oculus edid, take #1
2015-04-17 de-IPized version
2015-09-06 wip2
2015-09-06 rev2 sw working on rev1 pcb with DNA display
2015-09-15 rev2 working with DNA display
2015-09-16 E980: something starts to work!
2015-09-16 e980 @ 56 Hz
2015-10-06 dsi_core: LOCed the BUFPLLs to avoid P&R problems
2015-10-06 rtl: moved control regs to separate unit, added PLL reconfiguration
2015-10-06 top/rev2: optional support for uRV CPU softcore
2015-10-06 hdmi: proper patch for Xilinx IP
2015-10-06 sw: wip
2015-11-27 bootloader wip
2015-11-27 uRV arch files added
2015-11-27 hpdmc support files for RISC-V
2015-12-03 e980 & PLL DRP working
2015-12-09 hdl/pll_drp: latch PLL data out on DRDY
2015-12-09 hdl/sysctl: added PLL_FREQ register
2015-12-09 top/rev2: fixed cross-clock domain timing constraints
2015-12-09 top/rev2: bit-banged SPI flash & PLL reconf support
2015-12-09 sw/bootloader: increase RAM size to 32kB
2015-12-09 sw: fake I/O registers for UART used to speed up simulations
2015-12-09 sw: new FW with config menu & dynamic display switching, supports both IP4 and E980
2015-12-09 sw: increase user app memory size to 32k
2015-12-09 sw: forgot to add files for the new FW
2015-12-09 hdl: removed LM32 support. Now using uRV (RISC-V) as a submodule
2015-12-10 software: new bootloader, with flashing over USB support
2015-12-10 software: clean up Makefile, moved flash stuff to common dir, added missing files
2015-12-10 software: USB bootloader Python tool & RAM generator tools added
2015-12-10 software: code formatting, removing warnings, copyright stuff
2015-12-31 software: code formatting, removing warnings, copyright stuff hdl: missing manifests
2015-12-31 software: E980 & IP4 both work with dynamic reconf
2015-12-31 hdl: fixed PWM frequency for dimming the backlight
2016-01-05 hdl: fixed reset generator glitch
2016-01-05 software: correctly invoke bootloader in the Makefile
2017-04-27 added ISE project
2017-04-27 missing files added
2017-08-16 moved rev1 resign to a separate directory
2017-08-16 pcb/rev2: initial port of the schematics to KiCad
2017-08-23 pcb wip
2017-08-23 Completed port to KiCad, passes DRC+LVS. NOT MANUFACTURED.
2017-08-23 pcb/rev2: Completed rev2 PCB port to KiCad, passes DRC+LVS. NOT MANUFACTURED.
2019-04-20 rtl/dsi_core: initial version with AXI4 interfaces
2019-04-20 hdl/testbench: added AXI4 BFM
2019-04-20 hdl/testbench: trivial tb for AXI4 interfaces
2019-05-22 ip_cores: use latest version of urv-core
2019-05-22 axi4/zynq version: wip
2019-05-24 hdl: updated ISE project
2019-05-31 hdl: dsi_core: bring back colorbar generator
2019-06-03 debugging colorbar gen
2019-06-04 rtl/dsi_colorbar_gen: added handshake logic between TimingGen and ColorBarGen
2019-06-04 rtl/dsi_core: Vivado fixed by MODI
2019-06-04 rtl/dsi_packet_assembler: packer input byte count must be at least 2 pixels
2019-06-04 rtl: moved platform-dependent RTL sources to separate subdirectories
2019-06-04 testbench: added top-level TB with protocol decoding
2019-06-05 rtl/dsi_timing_gen: fix xilinx parse error
2019-06-05 rtl/dsi_core_zynq_wrapper: fix incorrect CLK_LP tristate connection
2019-06-06 dsi_packer: correctly handle 2-byte output
2019-06-06 dsi_core_zynq_wrapper: can't use HR I/O on 7z007, use PLL shifted clock for clock lane for Clock/Data align
2019-06-06 testbench/dsi_core: port to work with Vivado 2018.3's xsim
2019-06-16 dsi_core: added HS clock polarity control register
2019-07-06 rtl/dsi_colorbar_gen: support for 2 pixel per clock test screen
2019-07-06 rtl/dsi_core_zynq_wrapper: use correct clock frequency for LCD
2019-07-06 rtl/dsi_core: avoid pixel FIFO congestion when the timing generator is not yet initialized
